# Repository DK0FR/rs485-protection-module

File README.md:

# RS485 Protection Module

Überspannungs- und HF-Schutzmodul für RS485 und 24 V am Antennenrotor von DK0FR (DOK A05), DH5WM 2026, www.dk0fr.de

Das Modul sitzt hinter dem NEMA-17-Rotormotor in einem geerdeten Vierkantrohr. Es schützt Motor und Treiber vor zwei Dingen:

- Überspannungen, die bei Gewittern in die 30 m lange, ungeschirmte Steuerleitung einkoppeln
- HF-Einstreuung (1,8–30 MHz, bis 750 W) aus den benachbarten KW-Antennen

Jeder Pfad (24 V und RS485) durchläuft vier Stufen:

1. Ringkern
2. Grobschutz mit Gasableiter und Varistor
3. zweistufiger Gleichtaktfilter
4. TVS-Feinschutz

**Stand:** Rev. 4 vom 15.10.2026. Die Platine ist geroutet und gegen die Datenblätter geprüft, die Gerberdaten sind bestellfertig. Die Schaltung ist berechnet, aber noch nicht gemessen.

## Eckdaten

| | |
|---|---|
| Versorgung | 24 V DC (Netzteil ≤ 24,5 V), ausgelegt für 5 A, PTC 8 A |
| Bus | RS485 2-Draht, bis 115 200 Bd, Abschluss 120 Ω per Steckbrücke |
| Schutz | GDT 90 V, Varistor S14K30, SMCJ26A, SM712, Gleichtaktdrosseln 1 mH/32 µH und 2,2 mH/51 µH |
| Platine | 100 × 38 mm, 2 Lagen, 1,6 mm, 4 × M3 (PE ans Rohr) |

## Dokumentation

Die vollständige Dokumentation steht in **[doc/README.md](doc/README.md)**:

- [Schaltung](doc/README.md#3-schaltung) mit Schaltbildern für 24 V und RS485 und [Auslegung](doc/README.md#4-auslegung-und-entscheidungen)
- [Platine](doc/README.md#5-platine): Bestückungsplan, Layout, PE-Konzept, Drosselwicklungen, Netzklassen
- [Einbau und Anschluss](doc/README.md#6-einbau-und-anschluss) mit Klemmenbelegung
- [Stückliste](doc/README.md#7-stückliste) und [Leiterplatte bestellen](doc/README.md#8-leiterplatte-bestellen)
- [Bestückung](doc/README.md#9-bestückung) und [Prüfung und Inbetriebnahme](doc/README.md#10-prüfung-und-inbetriebnahme)
- [Prüfstand](doc/README.md#11-prüfstand-des-entwurfs) und [offene Punkte](doc/README.md#12-offene-punkte)

## Dateien

| Datei | Inhalt |
|---|---|
| [`rs485-protection-module.kicad_pro`](rs485-protection-module.kicad_pro), [`.kicad_sch`](rs485-protection-module.kicad_sch), [`.kicad_pcb`](rs485-protection-module.kicad_pcb) | KiCad-10-Projekt |
| [`doc/schaltplan.pdf`](doc/schaltplan.pdf) | Schaltplan als PDF |
| [`Fertigung/JLCPCB_Rev4/rs485-protection-module_Rev4_JLCPCB.zip`](Fertigung/JLCPCB_Rev4/rs485-protection-module_Rev4_JLCPCB.zip) | Gerber- und Bohrdaten für JLCPCB |
| [`Mouser-Bestellliste-Rotor-Schutzmodul (1).xlsx`](<Mouser-Bestellliste-Rotor-Schutzmodul (1).xlsx>) | Bestellliste für den Mouser-BOM-Import |
| [`doc/`](doc/) | Dokumentation und Abbildungen |

Repository: https://github.com/DK0FR/rs485-protection-module

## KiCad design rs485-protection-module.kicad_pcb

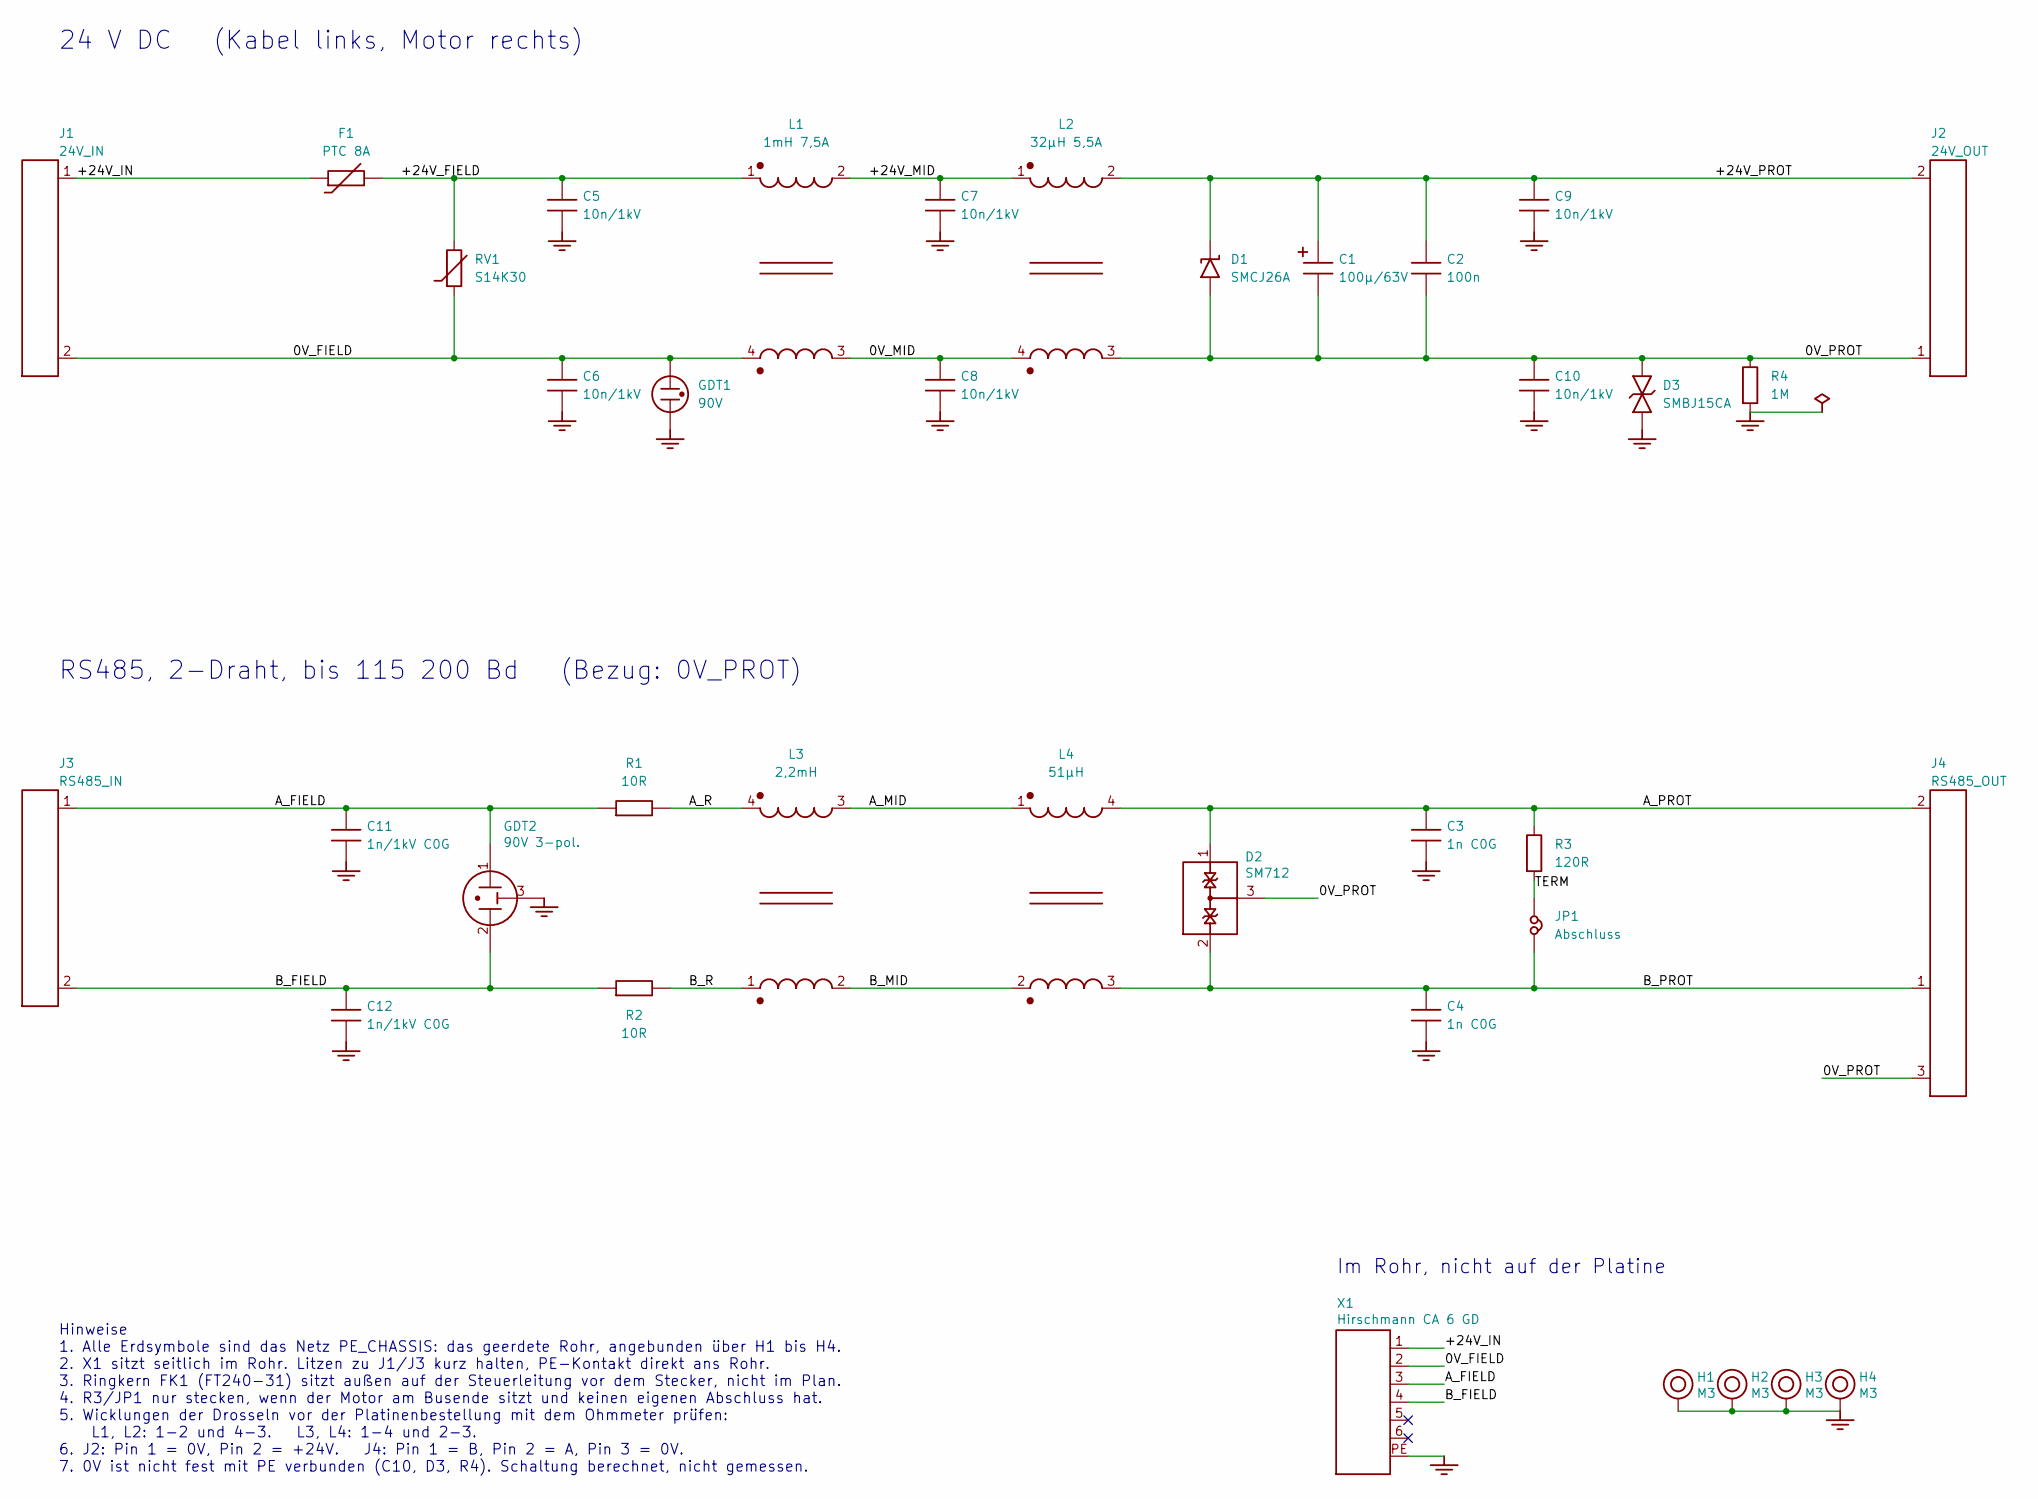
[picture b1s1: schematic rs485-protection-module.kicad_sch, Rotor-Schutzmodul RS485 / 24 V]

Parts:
C1: 100µ/63V; CP_Radial_D10.0mm_P5.00mm; MPN EEU-FC1J101
C2: 100n; C_1206_3216Metric_Pad1.33x1.80mm_HandSolder; MPN C1206C104K1RACTU
C3, C4: 1n C0G; C_1206_3216Metric_Pad1.33x1.80mm_HandSolder; MPN C1206C102JDGACTU
C5, C6, C7, C8, C9, C10: 10n/1kV; C_1206_3216Metric_Pad1.33x1.80mm_HandSolder; MPN C1206C103KDRACTU
C11, C12: 1n/1kV C0G; C_1206_3216Metric_Pad1.33x1.80mm_HandSolder; MPN C1206C102JDGACTU
D1: SMCJ26A; D_SMC_Handsoldering; MPN SMCJ26A
D2: SM712; SOT-23_Handsoldering; MPN SM712.TCT
D3: SMBJ15CA; D_SMB_Handsoldering; MPN SMBJ15CA
F1: PTC 8A; Fuse_PTC_Radial_P5.1mm_P10.2mm; MPN MF-R800
GDT1: 90V; GDT_Bourns_2035-xx-SM; MPN 2035-09-SM-RPLF
GDT2: 90V 3-pol.; GDT_Bourns_2036-xx-SM; MPN 2036-09-SM-RPLF
H1, H2, H3, H4: M3; MountingHole_3.2mm_M3_DIN965_Pad
J1: 24V_IN; TerminalBlock_Phoenix_MKDS-1,5-2-5.08_1x02_P5.08mm_Horizont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; MPN 1715721
J2: 24V_OUT; TerminalBlock_Phoenix_MKDS-1,5-2-5.08_1x02_P5.08mm_Horizont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; MPN 1715721
J3: RS485_IN; TerminalBlock_Phoenix_MKDS-1,5-2-5.08_1x02_P5.08mm_Horizont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; MPN 1715721
J4: RS485_OUT; TerminalBlock_Phoenix_MKDS-1,5-3-5.08_1x03_P5.08mm_Horizont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; MPN 1715734
JP1: Abschluss; PinHeader_1x02_P2.54mm_Vertical; MPN 60900213421
L1: 1mH 7,5A; L_CommonMode_Wuerth_WE-CMB-L_Pins1234; MPN 744824801
L2: 32µH 5,5A; L_CommonMode_Wuerth_WE-CMB-S; MPN 744842632
L3: 2,2mH; L_CommonModeChoke_Wuerth_WE-SL5; MPN 744272222
L4: 51µH; L_CommonMode_Wuerth_WE-SL2; MPN 744227
R1, R2: 10R; R_MELF_MMB-0207; MPN CMB02070X1009JB200
R3: 120R; R_1206_3216Metric_Pad1.30x1.75mm_HandSolder; MPN RC1206FR-07120RL
R4: 1M; R_1206_3216Metric_Pad1.30x1.75mm_HandSolder; MPN RC1206FR-071ML
RV1: S14K30; RV_Disc_D15.5mm_W4.5mm_P7.5mm; MPN B72214S0300K101
X1: Hirschmann CA 6 GD

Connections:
0V_FIELD: C6.1, GDT1.1, J1.2, L1.4, RV1.2, X1.2
0V_MID: C8.1, L1.3, L2.4
0V_PROT: C1.2, C2.2, C10.1, D1.2, D2.3, D3.1, J2.1, J4.3, L2.3, R4.1
+24V_FIELD: C5.1, F1.2, L1.1, RV1.1
+24V_IN: F1.1, J1.1, X1.1
+24V_MID: C7.1, L1.2, L2.1
+24V_PROT: C1.1, C2.1, C9.1, D1.1, J2.2, L2.2
A_FIELD: C11.1, GDT2.1, J3.1, R1.1, X1.3
A_MID: L3.3, L4.1
A_PROT: C3.1, D2.1, J4.2, L4.4, R3.1
A_R: L3.4, R1.2
B_FIELD: C12.1, GDT2.2, J3.2, R2.1, X1.4
B_MID: L3.2, L4.2
B_PROT: C4.1, D2.2, J4.1, JP1.2, L4.3
B_R: L3.1, R2.2
PE_CHASSIS: C3.2, C4.2, C5.2, C6.2, C7.2, C8.2, C9.2, C10.2, C11.2, C12.2, D3.2, GDT1.2, GDT2.3, H1.1, H2.1, H3.1, H4.1, R4.2, X1.PE
TERM: JP1.1, R3.2

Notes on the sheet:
Hinweise 1. Alle Erdsymbole sind das Netz PE_CHASSIS: das geerdete Rohr, angebunden über H1 bis H4. 2. X1 sitzt seitlich im Rohr. Litzen zu J1/J3 kurz halten, PE-Kontakt direkt ans Rohr. 3. Ringkern FK1 (FT240-31) sitzt außen auf der Steuerleitung vor dem Stecker, nicht im Plan. 4. R3/JP1 nur steck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
RS485, 2-Draht, bis 115 200 Bd (Bezug: 0V_PROT)
24 V DC (Kabel links, Motor rechts)
Im Rohr, nicht auf der Platine

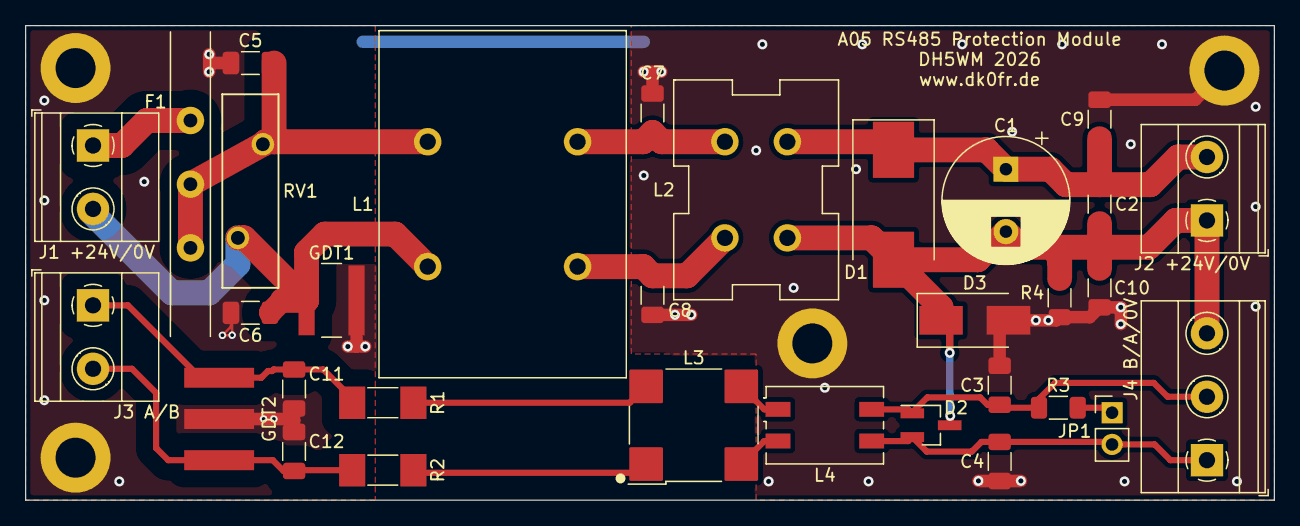
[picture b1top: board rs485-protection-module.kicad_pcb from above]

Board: 2 copper layers, 100.0 x 38.0 mm, 36 parts (0 on the bottom side), 17 nets.
